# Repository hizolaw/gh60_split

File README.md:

# gh60_modified (or gh60_split)
A split gh60 pcb design, software compatible with original `komar007/gh60`.

A sample generated gerber and BOM/POS for pcb and smt are avaliable in relaese tab.

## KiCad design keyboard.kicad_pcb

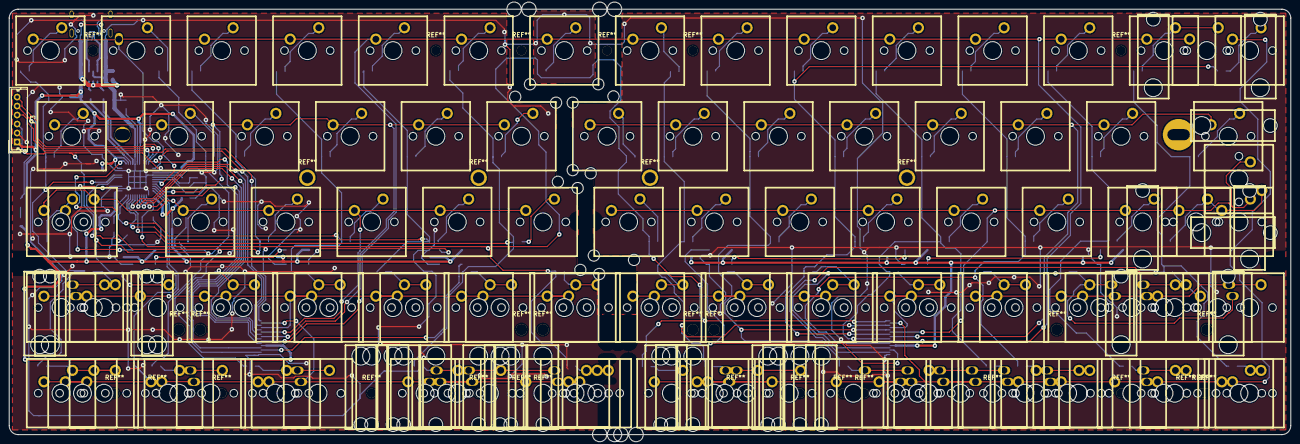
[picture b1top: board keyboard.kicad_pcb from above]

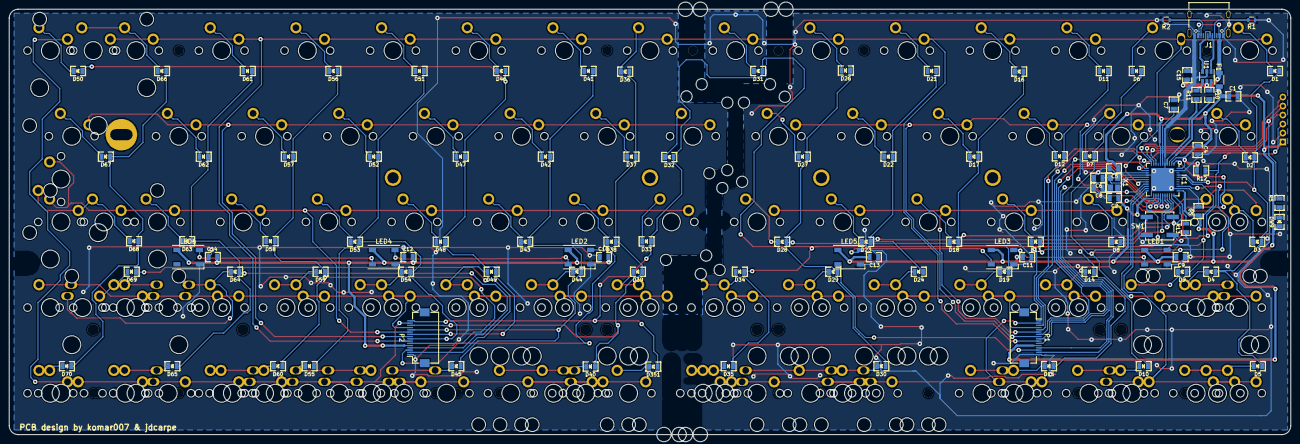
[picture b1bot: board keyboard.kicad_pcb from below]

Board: 2 copper layers, 285.0 x 94.6 mm, 302 parts (106 on the bottom side), 125 nets.

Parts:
C1, C7: 1u; 0805C
C2, C3, C4, C5, C9, C10, C11, C12, C13, C14, C15: 100n; 0805C
C6, C8: 22p; 0805C
D1, D2, D3, D4, D5, D6, D7, D8, D9, D10, D11, D12, D13, D14, D15, D16, D17, D18, D19, D21, D22, D23, D24, D26, D27, D28, D29, D30, D31, D32, D33, D34, D35, D36, D37, D38, D39, D40, D41, D42, D43, D44, D45, D46, D47, D48, D49, D50, D51, D52, D53, D54, D55, D56, D57, D58, D59, D60, D61, D62, D63, D64, D65, D66, D67, D68, D69, D70, D351: 1N4148; 0805D
DW9: LED; 0805D
F1: FUSE; C_1206
HOLE: VAL**; PKRH
HOLE#2, HOLE#3, HOLE#4, HOLE#5, HOLE#6, HOLE#7, HOLE#8, HOLE#9, HOLE#10, HOLE#11, HOLE#12, HOLE#13, HOLE#14, HOLE#15, HOLE#16, HOLE#17, HOLE#18, HOLE#19, HOLE#20, HOLE#21, HOLE#22, HOLE#23, HOLE#24, HOLE#25, HOLE#26, HOLE#27, HOLE#28, HOLE#30, HOLE#31, HOLE#32, HOLE#33, HOLE#34, HOLE#35, HOLE#36, HOLE#37, HOLE#38, HOLE#39, HOLE#40, HOLE#41, HOLE#42, HOLE#43, HOLE#44, HOLE#45, HOLE#46, HOLE#47, HOLE#48, HOLE#49, HOLE#51: VAL**; PKRH
HOLE#29, HOLE#50: VAL**; PKRHSL
HOLE#52: VAL**; PKRHC
IC1: ATMEGA32U4; QFN-44-1EP_7x7mm_Pitch0.5mm
J1: USBTYPEC; USB_C_Receptacle_Palconn_UTC16-G
LED1, LED2, LED3, LED4, LED5, LED6: WS2812B; LED_WS2812B-PLCC4
MXST: VAL**; MXST
MXST#2, MXST#3, MXST#4, MXST#5, MXST#6, MXST#7, MXST#8, MXST#9, MXST#10, MXST#11, MXST#12, MXST#13, MXST#14, MXST#15, MXST#16, MXST#17, MXST#18, MXST#19, MXST#20, MXST#21, MXST#22, MXST#23, MXST#24, MXST#25, MXST#26, MXST#27, MXST#28: VAL**; MXST
P1, P2: DIL16; Hirose_FH12-16S-0.5SH_1x16-1MP_P0.50mm_Horizontal
P3: CONN_6; Molex_MicroLatch-53253-0670_06x2.00mm_Straight
R1, R2: 5.1k; R_0603
R5: R; 0805R
R10, R11: 22; 0805R
R12, R13: 10k; 0805R
S1, S2, S3, S4, S5, S6, S7, S8, S10, S11, S12, S13, S14, S15, S16, S17, S18, S19, S21, S22, S23, S24, S26, S27, S28, S29, S30, S31, S32, S33, S34, S35, S36, S37, S38, S39, S40, S41, S42, S43, S44, S45, S46, S47, S48, S49, S51, S52, S53, S54, S55, S56, S57, S58, S59, S60, S61, S62, S65, S66, S67, S68, S69, S70: MX1A
S9, S50, S63, S64, S101, S102, S141, S151, S152, S191, S241, S291, S301, S302, S303, S304, S311, S341, S351, S352, S353, S391, S401, S402, S403, S411, S412, S441, S451, S491, S511, S512, S541, S551, S552, S553, S591, S601, S602, S603, S641, S642, S651, S652, S661, S681, S682, S691, S692, S693, S7012: MX1A; MX1A_no3d
SW1: SW_PUSH; SW_SPST_EVPBF
U1: USBLC6-2SC6; SOT-23-6
X1: ASX4; 4-SMD

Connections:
/CapsLED: IC1.10, P3.5, R5.1
/GPIO0: IC1.36, LED1.4
/GPIO0-r: LED2.4, P2.3
/GPIO0_out: LED5.2, P1.14
/VCC-r: C10.2, C12.2, C14.2, LED2.1, LED4.1, LED6.1, P2.5
/col1: D1.1, D2.1, D3.1, D4.1, D5.1, IC1.41
/col2: D6.1, D7.1, D8.1, D9.1, D10.1, IC1.40
/col3: D11.1, D12.1, D13.1, D14.1, D15.1, IC1.1
/col4: D16.1, D17.1, D18.1, D19.1, IC1.32
/col5: D21.1, D22.1, D23.1, D24.1, IC1.31
/col6: D26.1, D27.1, D28.1, D29.1, D30.1, IC1.30
/col7: D31.1, D32.1, D33.1, D34.1, D35.1, D351.1, IC1.25, P1.1, P2.16
/col8: IC1.9, P1.3, P3.4
/col8-r: D36.1, D37.1, D38.1, D39.1, D40.1, P2.14
/col9: IC1.12, P1.5
/col9-r: D41.1, D42.1, D43.1, D44.1, D45.1, P2.12
/col10: IC1.29, P1.7
/col10-r: D46.1, D47.1, D48.1, D49.1, D50.1, P2.10
/col11: IC1.28, P1.9
/col11-r: D51.1, D52.1, D53.1, D54.1, D55.1, P2.8
/col12: IC1.27, P1.11
/col12-r: D56.1, D57.1, D58.1, D59.1, D60.1, P2.6
/col13: IC1.26, P1.13
/col13-r: D61.1, D62.1, D63.1, D64.1, D65.1, P2.4
/col14: IC1.11, P1.15, P3.6
/col14-r: D66.1, D67.1, D68.1, D69.1, D70.1, P2.2
/row1: IC1.18, P1.10, P2.7, S1.1, S6.1, S11.1, S16.1, S21.1, S26.1, S31.1, S36.1, S41.1, S46.1, S51.1, S56.1, S61.1, S66.1, S661.1
/row2: IC1.19, P1.8, S2.1, S7.1, S12.1, S17.1, S22.1, S27.1
/row2-r: P2.9, S32.1, S37.1, S42.1, S47.1, S52.1, S57.1, S62.1, S67.1
/row3: IC1.20, P1.6, S3.1, S8.1, S13.1, S18.1, S23.1, S28.1, S311.2
/row3-r: P2.11, S33.1, S38.1, S43.1, S48.1, S53.1, S58.1, S63.1, S68.1, S681.1, S682.2
/row4: IC1.21, P1.4, S4.1, S9.1, S14.1, S19.1, S24.1, S29.1, S34.1, S141.1, S191.1, S241.1, S291.1, S341.1, S411.1, S412.1
/row4-r: P2.13, S39.1, S44.1, S49.1, S54.1, S59.1, S64.1, S69.1, S391.1, S441.1, S491.1, S541.1, S591.1, S641.2, S642.1, S691.2, S692.1, S693.1
/row5: IC1.22, P1.2, S5.1, S10.1, S15.1, S30.1, S35.1, S101.1, S102.1, S151.1, S152.1, S301.1, S302.1, S303.1, S304.1, S351.1, S352.1, S511.1, S512.1
/row5-r: P2.15, S40.1, S45.1, S50.1, S55.1, S60.1, S65.1, S70.1, S353.1, S401.1, S402.1, S403.1, S451.1, S551.1, S552.1, S553.1, S601.1, S602.1, S603.1, S651.1, S652.1, S7012.1
GND: C1.2, C2.2, C3.2, C4.2, C5.2, C6.2, C7.2, C8.2, C9.1, C10.1, C11.1, C12.1, C13.1, C14.1, C15.2, IC1.5, IC1.15, IC1.23, IC1.35, IC1.43, IC1.45, J1.A1, J1.A12, J1.B1, J1.B12, LED1.3, LED2.3, LED3.3, LED4.3, LED5.3, LED6.3, P1.16, P2.1, P3.2, R1.1, R2.1, R13.1, SW1.2, U1.2, X1.2, X1.4
unnamed: C6.1, IC1.16, X1.1
unnamed: C7.1, IC1.6
unnamed: C8.1, IC1.17, X1.3
unnamed: C15.1, F1.1, J1.A4, J1.A9, J1.B4, U1.5
unnamed: D1.2, S1.2
unnamed: D2.2, S2.2
unnamed: D3.2, S3.2, S311.1
unnamed: D4.2, S4.2, S411.2, S412.2
unnamed: D5.2, S5.2, S511.2, S512.2
unnamed: D6.2, S6.2
unnamed: D7.2, S7.2
unnamed: D8.2, S8.2
unnamed: D9.2, S9.2
unnamed: D10.2, S10.2, S101.2, S102.2
unnamed: D11.2, S11.2
unnamed: D12.2, S12.2
unnamed: D13.2, S13.2
unnamed: D14.2, S14.2, S141.2
unnamed: D15.2, S15.2, S151.2, S152.2
unnamed: D16.2, S16.2
unnamed: D17.2, S17.2
unnamed: D18.2, S18.2
unnamed: D19.2, S19.2, S191.2
unnamed: D21.2, S21.2
unnamed: D22.2, S22.2
unnamed: D23.2, S23.2
unnamed: D24.2, S24.2, S241.2
unnamed: D26.2, S26.2
unnamed: D27.2, S27.2
unnamed: D28.2, S28.2
unnamed: D29.2, S29.2, S291.2
unnamed: D30.2, S30.2, S301.2, S302.2, S303.2, S304.2
unnamed: D31.2, S31.2
unnamed: D32.2, S32.2
unnamed: D33.2, S33.2
unnamed: D34.2, S34.2, S341.2
unnamed: D35.2, S35.2, S351.2, S352.2
unnamed: D36.2, S36.2
unnamed: D37.2, S37.2
unnamed: D38.2, S38.2
unnamed: D39.2, S39.2, S391.2
unnamed: D40.2, S40.2, S401.2, S402.2, S403.2
unnamed: D41.2, S41.2
unnamed: D42.2, S42.2
unnamed: D43.2, S43.2
unnamed: D44.2, S44.2, S441.2
unnamed: D45.2, S45.2, S451.2
unnamed: D46.2, S46.2
unnamed: D47.2, S47.2
unnamed: D48.2, S48.2
unnamed: D49.2, S49.2, S491.2
unnamed: D50.2, S50.2
unnamed: D51.2, S51.2
unnamed: D52.2, S52.2
unnamed: D53.2, S53.2
unnamed: D54.2, S54.2, S541.2
unnamed: D55.2, S55.2, S551.2, S552.2, S553.2
unnamed: D56.2, S56.2
unnamed: D57.2, S57.2
unnamed: D58.2, S58.2
unnamed: D59.2, S59.2, S591.2
unnamed: D60.2, S60.2, S601.2, S602.2, S603.2
unnamed: D61.2, S61.2
unnamed: D62.2, S62.2
unnamed: D63.2, S63.2
unnamed: D64.2, S64.2, S641.1, S642.2
unnamed: D65.2, S65.2, S651.2, S652.2
unnamed: D66.2, S66.2, S661.2
unnamed: D67.2, S67.2
unnamed: D68.2, S68.2, S681.2, S682.1
unnamed: D69.2, S69.2, S691.1, S692.2, S693.2
unnamed: D70.2, S70.2, S7012.2
unnamed: D351.2, S353.2
unnamed: DW9.2, R5.2
unnamed: IC1.3, R10.2
unnamed: IC1.4, R11.1
unnamed: IC1.13, P3.3, R12.1, SW1.1
unnamed: IC1.33, R13.2
unnamed: J1.A5, R1.2
unnamed: J1.A6, J1.B6, U1.3
unnamed: J1.A7, J1.B7, U1.1
unnamed: J1.B5, R2.2
unnamed: LED1.2, LED3.4
unnamed: LED2.2, LED4.4
unnamed: LED3.2, LED5.4
unnamed: LED4.2, LED6.4
unnamed: R10.1, U1.6
unnamed: R11.2, U1.4
VCC: C1.1, C2.1, C3.1, C4.1, C5.1, C9.2, C11.2, C13.2, DW9.1, F1.2, IC1.2, IC1.7, IC1.14, IC1.24, IC1.34, IC1.44, LED1.1, LED3.1, LED5.1, P1.12, P3.1, R12.2

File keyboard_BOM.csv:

"Comment","Description","Designator","Footprint","LibRef","Pins","Quantity","PartNumber","url",
"1u","desc","C1,C7,","0805C","libref","2","2","","",
"100n","desc","C2,C3,C4,C5,C9,C10,C11,C12,C13,C14,C15,","0805C","libref","2","11","","",
"22p","desc","C6,C8,","0805C","libref","2","2","","",
"1N4148","desc","D46,D42,D43,D22,D38,D37,D41,D36,D32,D33,D23,D31,D21,D19,D18,D17,D16,D29,D28,D27,D26,D14,D13,D12,D11,D30,D15,D10,D39,D34,D24,D56,D61,D66,D57,D62,D67,D53,D58,D63,D68,D55,D60,D65,D70,D69,D64,D59,D54,D49,D44,D52,D51,D47,D48,D50,D1,D2,D3,D4,D5,D6,D7,D8,D9,D40,D35,D45,D351,","0805D","libref","2","69","","",
"LED","desc","DW9,","0805D","libref","2","1","","",
"FUSE","desc","F1,","C_1206","libref","2","1","","",
"ATMEGA32U4","desc","IC1,","QFN-44-1EP_7x7mm_Pitch0.5mm","libref","60","1","","",
"WS2812B","desc","LED6,LED1,LED2,LED3,LED4,LED5,","LED_WS2812B-PLCC4","libref","4","6","","",
"DIL16","desc","P1,P2,","Hirose_FH12-16S-0.5SH_1x16-1MP_P0.50mm_Horizontal","libref","18","2","","",
"5.1k","desc","R1,R2,","R_0603","libref","2","2","","",
"22","desc","R10,R11,","0805R","libref","2","2","","",
"10k","desc","R12,R13,","0805R","libref","2","2","","",
"R","desc","R5,","0805R","libref","2","1","","",
"SW_PUSH","desc","SW1,","SW_SPST_EVPBF","libref","4","1","","",
"USBLC6-2SC6","desc","U1,","SOT-23-6","libref","6","1","","",
"ASX4","desc","X1,","4-SMD","libref","4","1","","",
"Through Hole Items ",
"VAL**","desc","HOLE,","PKRHC","libref","1","1","","",
"VAL**","desc","HOLE,HOLE,HOLE,HOLE,HOLE,HOLE,HOLE,HOLE,HOLE,HOLE,HOLE,HOLE,HOLE,HOLE,HOLE,HOLE,HOLE,HOLE,HOLE,HOLE,HOLE,HOLE,HOLE,HOLE,HOLE,HOLE,HOLE,HOLE,HOLE,HOLE,HOLE,HOLE,HOLE,HOLE,HOLE,HOLE,HOLE,HOLE,HOLE,HOLE,HOLE,HOLE,HOLE,HOLE,HOLE,HOLE,HOLE,HOLE,HOLE,","PKRH","libref","1","49","","",
"VAL**","desc","HOLE,HOLE,","PKRHSL","libref","1","2","","",
"VAL**","desc","MXST,MXST,MXST,MXST,MXST,MXST,MXST,MXST,MXST,MXST,MXST,MXST,MXST,MXST,MXST,MXST,MXST,MXST,MXST,MXST,MXST,MXST,MXST,MXST,MXST,MXST,MXST,MXST,","MXST","libref","2","28","","",
"CONN_6","desc","P3,","Molex_MicroLatch-53253-0670_06x2.00mm_Straight","libref","6","1","","",
"MountingHole_2.5mm","desc","REF**,REF**,REF**,REF**,REF**,REF**,REF**,REF**,REF**,REF**,REF**,REF**,REF**,REF**,REF**,REF**,REF**,REF**,REF**,REF**,REF**,REF**,REF**,REF**,REF**,REF**,REF**,REF**,REF**,REF**,REF**,REF**,REF**,REF**,","MountingHole_2.5mm","libref","1","34","","",
"MX1A","desc","S6,S54,S48,S8,S24,S19,S29,S49,S34,S36,S33,S59,S39,S28,S41,S55,S12,S13,S14,S16,S2,S7,S1,S61,S38,S31,S32,S37,S42,S46,S51,S22,S27,S47,S52,S57,S67,S18,S23,S11,S26,S56,S66,S17,S69,S5,S15,S30,S60,S65,S70,S43,S58,S68,S44,S10,S21,S62,S53,S3,S40,S4,S35,S45,","MX1A","libref","5","64","","",
"MX1A","desc","S7012,S302,S401,S511,S311,S682,S601,S641,S101,S552,S151,S301,S691,S661,S50,S681,S692,S64,S63,S9,S411,S402,S351,S352,S141,S191,S241,S291,S303,S341,S353,S391,S403,S412,S441,S491,S512,S541,S591,S602,S642,S651,S652,S693,S551,S451,S102,S152,S304,S553,S603,","MX1A_no3d","libref","5","51","","",
"USBTYPEC","desc","J1,","USB_C_Receptacle_Palconn_UTC16-G","libref","22","1","","",

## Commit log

2019-04-25 split gh60
2019-04-28 align diode
2019-05-01 adjust diode position and track
2019-05-10 add switch S35 to scan matrix
2019-05-10 make split holes larger
2019-05-19 support 5/6 split or 6/7 split
2019-05-21 add r4_leftshift and related r5 layout
2019-05-27 fix gen_production_bom_pos script
2019-06-27 change to 4x4mm 4-pin button
2019-06-27 change usb to type-c
2019-06-27 add mounting hole at edges
2019-06-27 add 6 5x5mm ws2812b
2019-06-27 change C9-C15's field value from 100nF to 100n
2019-06-29 update BOM and POS files
2019-07-07 add ESD protector, overcurrent protector; add cc1/2 pulldown resistor
2019-07-10 add a 100n capacitor for VBUS-GND
2019-07-11 fix mounting holes on row5
2019-07-12 support hhkb layout
2019-07-13 change atmega32u4 footprint to QFN-44
2019-07-13 cleanup DRC warnings and adjust LEDs/reset_button position
2019-07-13 cleanup and generate production_files
2019-07-13 remove origin BOM
2019-07-14 change ISP pinout connector to 2.0mm x 6
2019-07-17 cleanup trackes
2019-07-21 atmega32u4 revert to tqfp-44 footprint
2019-08-19 Revert "atmega32u4 revert to tqfp-44 footprint"; cleanup track
    This reverts commit 0be7f9dd8754c97c2902cada8b6809ad15e07456.
